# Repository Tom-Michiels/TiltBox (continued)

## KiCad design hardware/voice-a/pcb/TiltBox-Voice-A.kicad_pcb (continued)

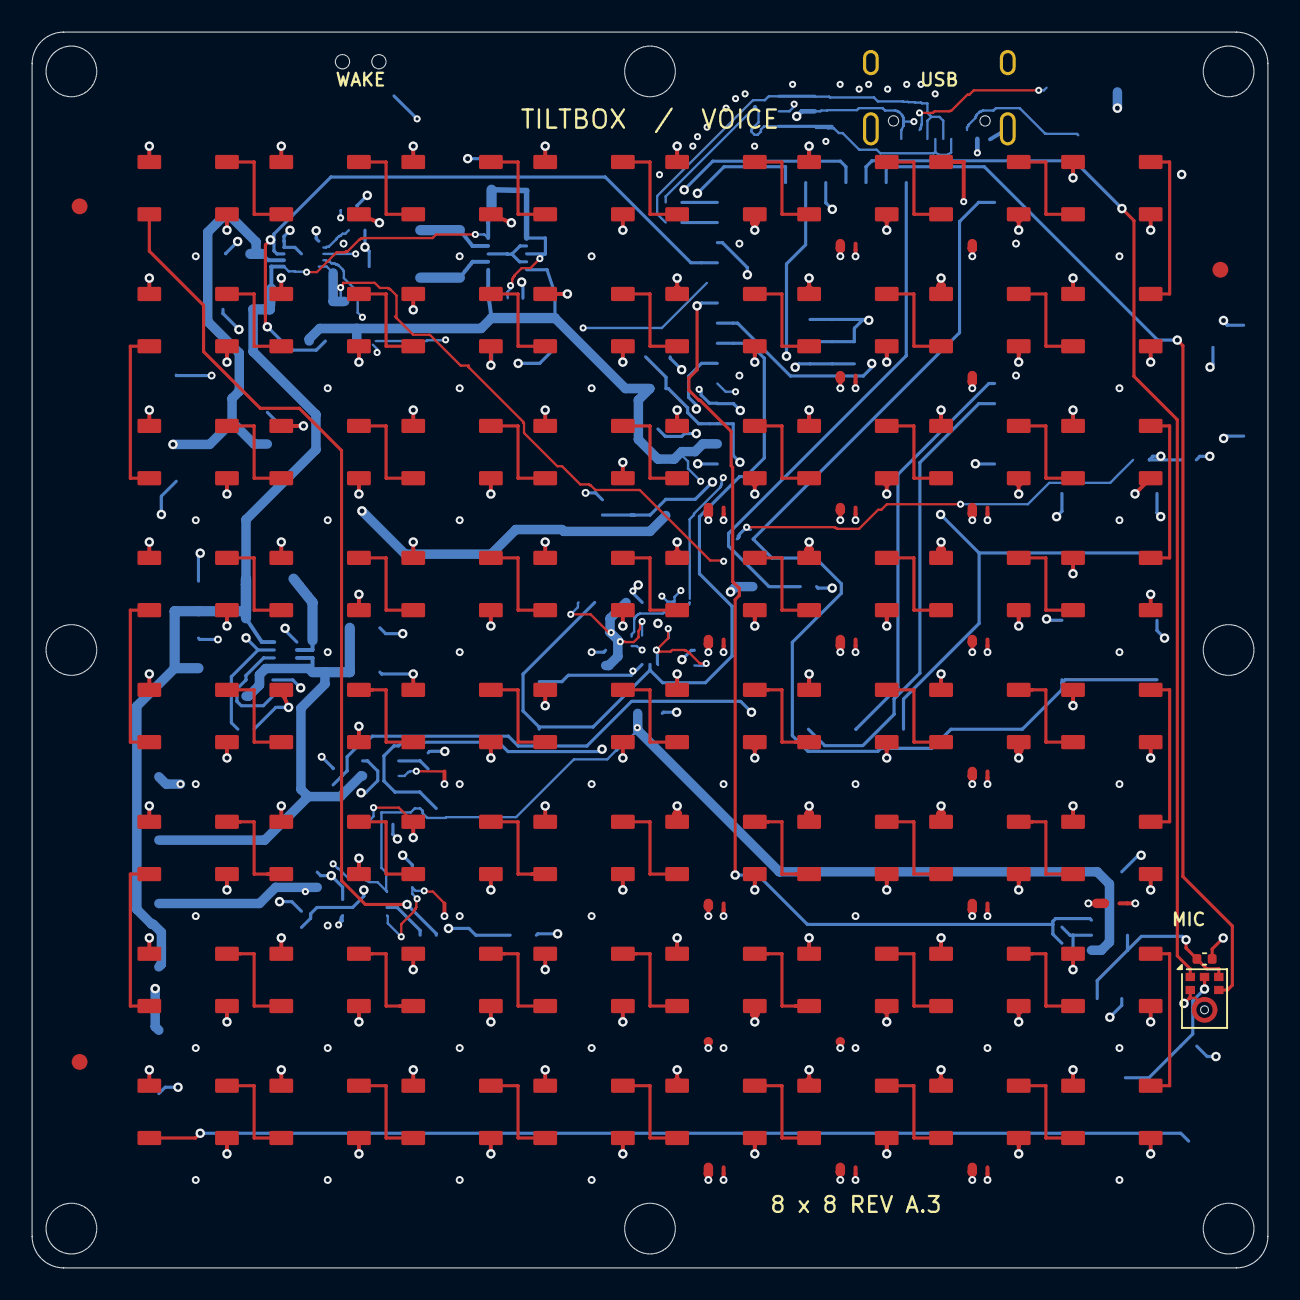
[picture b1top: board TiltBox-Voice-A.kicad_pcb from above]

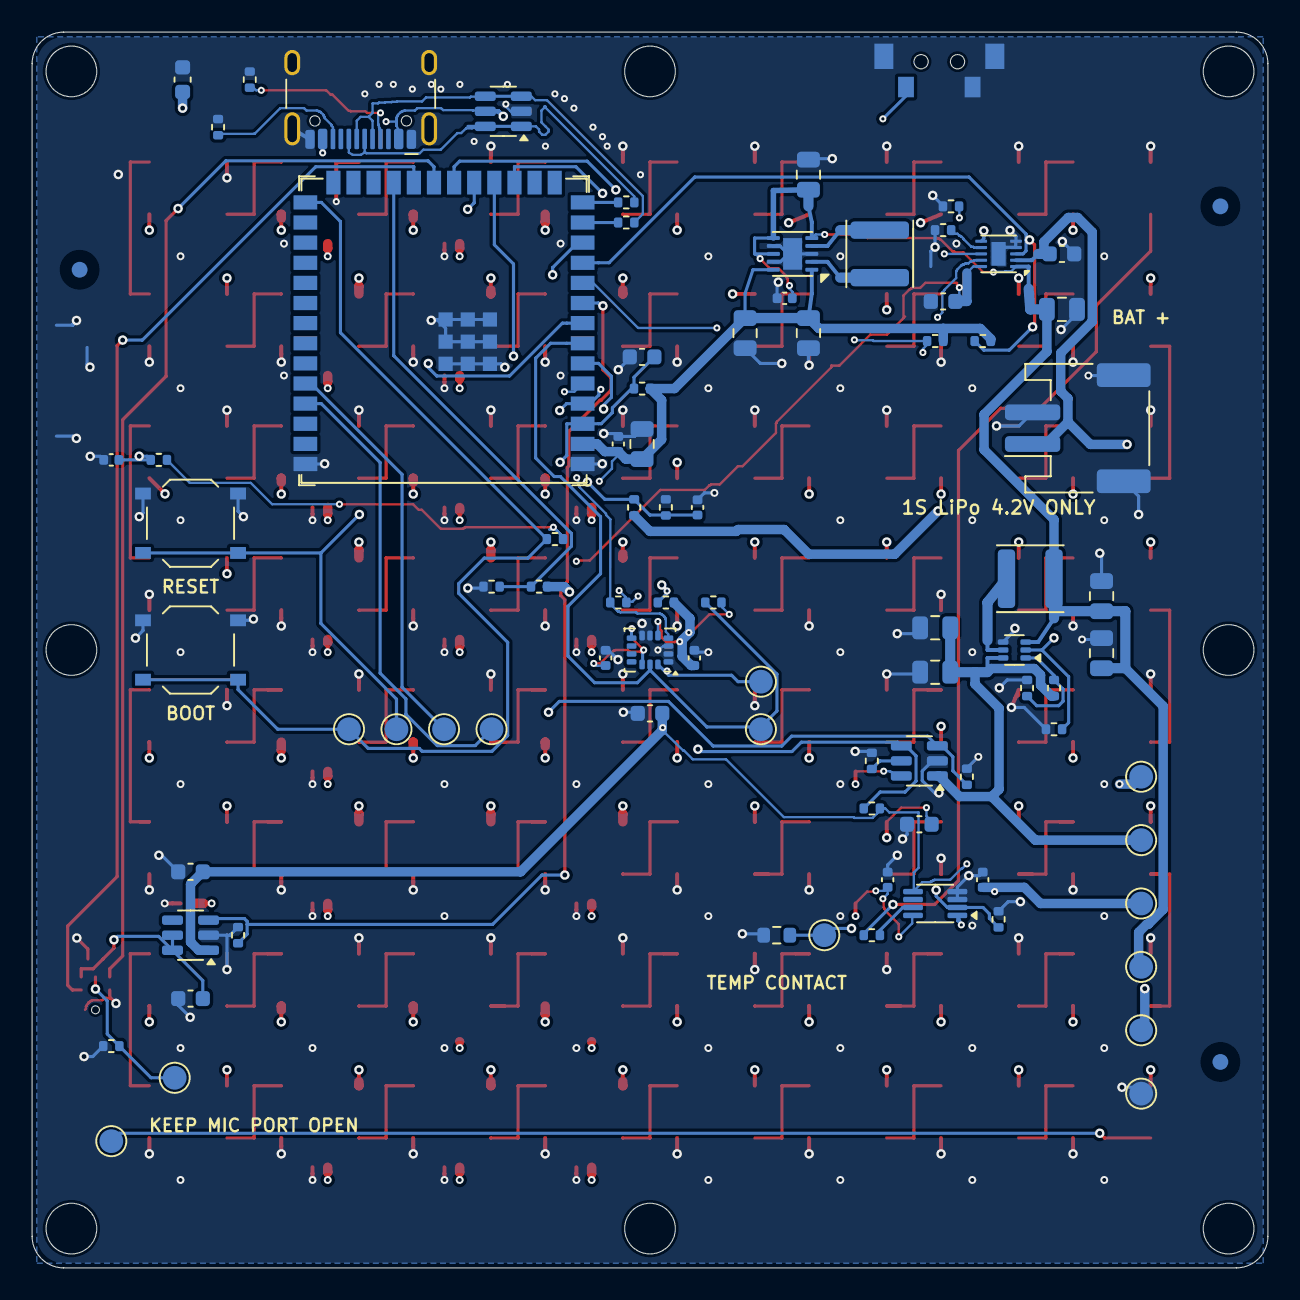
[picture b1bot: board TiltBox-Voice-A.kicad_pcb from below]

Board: 4 copper layers, 78.0 x 78.0 mm, 165 parts (88 on the bottom side), 108 nets.

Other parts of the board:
FID1, FID2, FID3, FID4, FID5, FID6: Fiducial 1mm / mask 2mm
H1, H2, H3, H4, H5, H6, H7, H8: M3 / NPTH 3.2; MountingHole_3.2mm_M3

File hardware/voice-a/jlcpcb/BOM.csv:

"Comment","Designator","Footprint","JLCPCB Part #","Quantity"
"1u","C65,C66,C68,C77,C82,C87,C88,C89","Capacitor_SMD:C_0603_1608Metric","C15849","8"
"22u","C67,C69,C71,C72,C73,C74,C75,C76,C80","Capacitor_SMD:C_0805_2012Metric","C45783","9"
"100n","C70,C78,C79,C81,C83,C84,C85,C86,C90","Capacitor_SMD:C_0402_1005Metric","C1525","9"
"WS2812B-B/T (V5)","D1,D2,D3,D4,D5,D6,D7,D8,D9,D10,D11,D12,D13,D14,D15,D16,D17,D18,D19,D20,D21,D22,D23,D24,D25,D26,D27,D28,D29,D30,D31,D32,D33,D34,D35,D36,D37,D38,D39,D40,D41,D42,D43,D44,D45,D46,D47,D48,D49,D50,D51,D52,D53,D54,D55,D56,D57,D58,D59,D60,D61,D62,D63,D64","LED_SMD:LED_WS2812B_PLCC4_5.0x5.0mm_P3.2mm","C2761795","64"
"USBLC6-2SC6","D65","Package_TO_SOT_SMD:SOT-23-6","C2687116","1"
"TYPE-C 16PIN 2MD(073)","J1","Connector_USB:USB_C_Receptacle_HCTL_HC-TYPE-C-16P-01A","C2765186","1"
"S2B-PH-SM4-TB(LF)(SN)","J2","Connector_JST:JST_PH_S2B-PH-SM4-TB_1x02-1MP_P2.00mm_Horizontal","C295747","1"
"FNR4018S1R5MT","L1","Inductor_SMD:L_Changjiang_FNR4018S","C167802","1"
"FNR4018S1R0MT","L2","Inductor_SMD:L_Changjiang_FNR4018S","C167801","1"
"5k1","R1,R2","Resistor_SMD:R_0402_1005Metric","C25905","2"
"22","R3,R4","Resistor_SMD:R_0402_1005Metric","C25092","2"
"18k","R5","Resistor_SMD:R_0402_1005Metric","C25762","1"
"1k","R6","Resistor_SMD:R_0402_1005Metric","C11702","1"
"10k","R7,R8,R14,R17,R18","Resistor_SMD:R_0402_1005Metric","C25744","5"
"732k","R9","Resistor_SMD:R_0402_1005Metric","C27016","1"
"100k","R10,R11,R13,R16,R19,R22,R26,R27,R28","Resistor_SMD:R_0402_1005Metric","C25741","9"
"49k9","R12","Resistor_SMD:R_0402_1005Metric","C25897","1"
"33","R15","Resistor_SMD:R_0402_1005Metric","C25105","1"
"1M","R20,R21","Resistor_SMD:R_0402_1005Metric","C26083","2"
"150k","R23","Resistor_SMD:R_0402_1005Metric","C25755","1"
"4k7","R24,R25","Resistor_SMD:R_0402_1005Metric","C25900","2"
"TS-1101VS-C-A-A","SW1","TiltBoxA:KEY-SMD_TS-1101VS-C-A-A","C318936","1"
"TS-1187A-B-A-B","SW2,SW3","Button_Switch_SMD:SW_Push_1P1T_XKB_TS-1187A","C318884","2"
"SDNT1608X103F3435FTF","TH1","Resistor_SMD:R_0603_1608Metric","C525660","1"
"ESP32-S3-WROOM-1U-N16R8","U1","TiltBoxA:ESP32-S3-WROOM-1U","C3013946","1"
"BQ25185DLHR","U2","Package_DFN_QFN:Texas_DLH0010A_WSON-10-1EP_2.2x2mm_P0.4mm_EP0.9x1.5mm","C19725033","1"
"TPS63031DSKR","U3","Package_SON:WSON-10-1EP_2.5x2.5mm_P0.5mm_EP1.2x2mm","C15516","1"
"TPS61023DRLR","U4","Package_TO_SOT_SMD:SOT-563","C919459","1"
"TPS2553DBVR-1","U5","Package_TO_SOT_SMD:SOT-23-6","C111738","1"
"SN74LVC2T45DCUR","U6","Package_SO:VSSOP-8_2.3x2mm_P0.5mm","C15741","1"
"LSM6DS3TR-C","U7","Package_LGA:LGA-14_3x2.5mm_P0.5mm_LayoutBorder3x4y","C967633","1"
"ICS-43434","U8","Sensor_Audio:InvenSense_ICS-43434-6_3.5x2.65mm","C5656610","1"
"TPS22918DBVR","U9","Package_TO_SOT_SMD:SOT-23-6","C131941","1"

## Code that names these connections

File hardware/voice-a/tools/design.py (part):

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
ROOT = Path(__file__).resolve().parents[1]
PARTS = []
GPIO = {'WAKE_N':4,'IMU_INT_N':5,'I2C_SDA':6,'I2C_SCL':7,'BAT_ADC':8,
        'LED_FAULT_N':9,'BOOST_EN':10,'LED_EN':11,'LED_DATA_3V3':12,
        'MIC_WS':13,'MIC_BCLK':14,'MIC_SD':15,'MIC_EN':16,
        'CHG_STAT1':17,'CHG_STAT2':18,'USB_DM':19,'USB_DP':20,'VBUS_SENSE':21}
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 19:11,20:12,21:13,22:14,23:21,24:47,25:48,26:45,27:0,28:35,29:36,30:37,31:38,
 32:39,33:40,34:41,35:42,36:44,37:43,38:2,39:1}
pinout={k:next((n for n,g in GPIO.items() if g==gpio), None) for k,gpio in esp_gpio.items()}
pinout.update({1:'GND',2:'3V3',3:'ESP_EN',27:'BOOT_N',36:'UART_RX',37:'UART_TX',40:'GND',41:'GND'})
add('U1','ESP32-S3-WROOM-1U-N16R8','TiltBoxA:ESP32-S3-WROOM-1U','C3013946',pinout,(13,-20),0,sheet='logic',
    names={**{k:'GPIO'+str(g) for k,g in esp_gpio.items()},1:'GND',2:'3V3',3:'EN',40:'GND',41:'EP_GND'},
    types={**{k:'bidirectional' for k in esp_gpio},1:'power_in',2:'power_in',3:'input',40:'passive',41:'passive'})
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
